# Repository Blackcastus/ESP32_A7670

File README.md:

# ph_portable_refrigerator_v2_hw

Designer: Mr.Duc_Hien

## Lưu ý thiết kế Hardware.
- Khóa cửa thường hở 12V (dài x rộng x cao tối thiểu 49mm x 30mm x 20mm). -> check notOK
- Vị trí cổng USB trên tủ thay bằng khay sim. -> check OK
- Thêm led status cho simcom và PGS.
- Sử dụng các loại header cắp khác nhau để không bị cắm nhầm.
- Kiếm lại lò xo cho button.
- Thiết kế lại bus cắm LCD.
- Chú ý căn chỉnh LCD cho khớp với vỏ tủ.
- Kiếm lại IC UART - I2C chp bộ BMS.
- Thêm RS485 viết bằng software uart.

## Hồ sơ đặc tả tủ lạnh di đông.

[Mô tả tủ lạnh di động](./Mota_TuLanhDiDong.pdf)

## Block diagram.

## Hardware MCU và Display

1. **Hardware board MCU.**

    **1.1. Thông số kỹ thuật board MCU:**

    * Nguồn input 12V được lấy từ bộ pin 12V hoặc qua adapter 12V.
    * MCU : ESP32-WROOM, debug qua USB.
    * Cảm biến: nhiệt độ PT100, cảm biến cửa.
    * Lấy vị trí GPS.
    * Kết nối module SIM 3G.
    * Đọc/lưu thời gian thực qua RTC.
    * Lưu dữ liệu vào thẻ nhớ.
    * Kết nối với màn hình LCD TFT 2Inch.
    * kết nối với bàn phím cảm ứng.
    * Có RS485 (sử dụng code software serial mới dùng được).
    * Điều khiển block lạnh.
    * Điều khiển khóa tủ.
    * Điều khiển đèn chiếu sáng trong tủ.
    * Điều khiểu chuông báo.
    * Đọc dữ liệu quản lý pin từ daly BMS.
    
    **1.2. Hình ảnh bộ quản lý pin BMS**

    **1.3. Hình ảnh board**

    Top layer

    Bottom layer

    Top 3D

    Bottom 3D

2. Hardware board display.

    **2.1. Thông số kỹ thuật board display**
    * Điện áp: 3V3.
    * Giao tiếp với LCD qua giao thức SPI.
    * Giao tiếp với bàn phím cảm ứng qua giao thức I2C.
    * Có chuông báo.

    **2.2. Hình ảnh board**

    Top layer

    Bottom layer

    Top 3D

    Bottom 3D

    Board sau khi hàn

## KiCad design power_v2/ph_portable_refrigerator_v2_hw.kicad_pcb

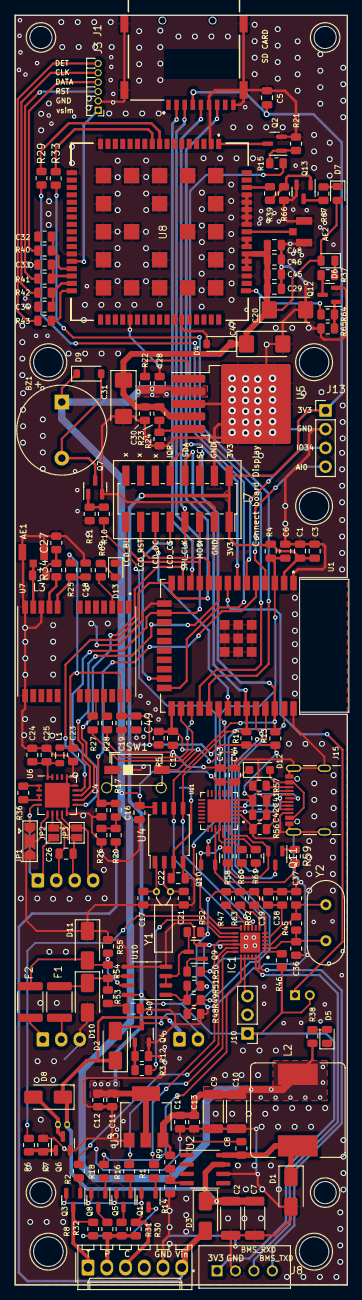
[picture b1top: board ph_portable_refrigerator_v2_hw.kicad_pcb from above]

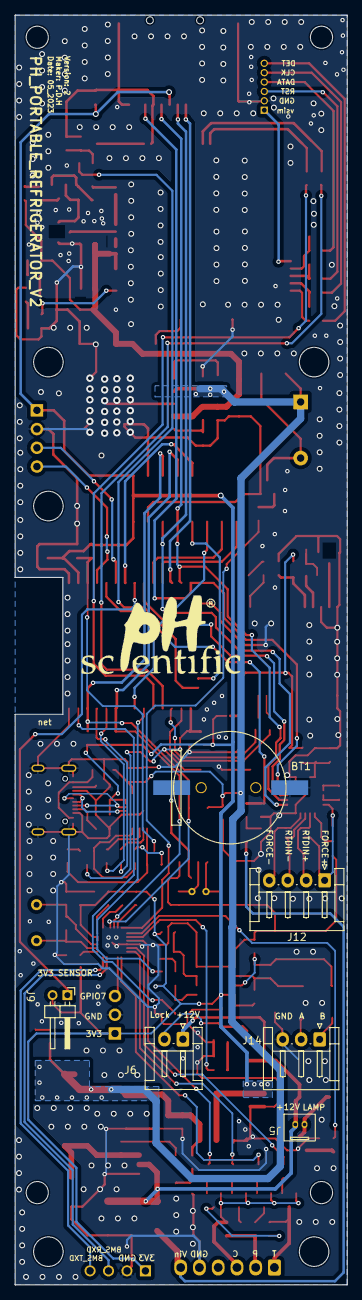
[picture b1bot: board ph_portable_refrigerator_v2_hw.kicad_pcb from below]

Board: 2 copper layers, 45.0 x 172.0 mm, 179 parts (6 on the bottom side), 131 nets.

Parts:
AE1: GPS; Antenna_RF
AE2: gsm; Antenna_RF
BT1: cr1220; BT_CR1220
BZ1: Buzzer-Device; Buzzer_12x9.5RM7.6
C1, C6, C15, C18, C22, C29, C41, C43: 10uF; C_0805_2012Metric
C2, C7, C9, C10: 10uF; R_2010_5025Metric
C3, C5, C16, C26, C40, C42, C44, C45, C49: 100nF; C_0805_2012Metric
C4, C12, C14, C25, C38: 100nF; R_0805_2012Metric
C8, C27: 10nF; R_0805_2012Metric
C11, C13, C28, C39: 10uF; R_0805_2012Metric
C17, C21: 7pF; R_0805_2012Metric
C19: 1uF; C_0805_2012Metric
C20, C31, C47: 100uF; CP_EIA-6032-15_Kemet-U
C23, C24, C30: 1uF; R_0805_2012Metric
C32, C33, C34: 22pF; R_0805_2012Metric
C36, C37: 18pF; R_0805_2012Metric
C46: 33pF; C_0805_2012Metric
C48: 10pF; C_0805_2012Metric
D1, D3: SS3x_SMA; D_SMA
D2: m7; D_SMA
D4: 5.1V; D_SOD-123
D5: RED; LED_0805_2012Metric
D6, D7, D13: blue; LED_0805_2012Metric
D8: M7; D_SMA
D9: 1N4148_T4; D_SOD-123
D10, D11: D_TVS; D_SMA
D12: 1N4007_T7; D_SOD-123F
F1, F2: Fuse; Fuse_SMD_1812
IC1: SC16IS750IBS,128; QFN50P400X400X100-25N
J1: microSD_Card
J3: Conn_01x06_Pin; PinHeader_1x06_P1.27mm_Horizontal
J5: lamp; Header_2P_1.25mm
J6: lock_latch; JST_EH_S2B-EH_1x02_P2.50mm_Horizontal
J7: Conn_02x08_Odd_Even; PinSocket_2x08_P2.00mm_Vertical_SMD
J8: Header_4P_2.54mm
J9: sensor; PinHeader_1x02_P2.00mm_Horizontal
J10: Extra; PinHeader_1x03_P2.54mm_Vertical
J11: refrigerator; Molex_KK-254_AE-6410-06A_1x06_P2.54mm_Vertical
J12: Conn_01x04; JST_EH_S4B-EH_1x04_P2.50mm_Horizontal
J13: Extra; PinHeader_1x04_P2.54mm_Vertical
J14: Conn_01x03_Pin; JST_EH_S3B-EH_1x03_P2.50mm_Horizontal
J15: USB_C_Receptacle_USB2.0; USB_C_Receptacle_GCT_USB4105-xx-A_16P_TopMnt_Horizontal
JP1: SolderJumper_3_Bridged12; SolderJumper-3_P2.0mm_Open_TrianglePad1.0x1.5mm
JP2, JP3: SolderJumper_2_Open; SolderJumper-2_P1.3mm_Open_Pad1.0x1.5mm
L1: L600R; L_0805_2012Metric
L2: 15uH; L_Bourns_SRR1260
L3: 22uH; R_0805_2012Metric
Q1, Q3, Q5, Q8, Q10, Q11: C1815; SOT-23
Q2, Q7, Q12, Q13: C1815_SOT23; SOT-23
Q4: AO3400A; SOT-23-3
Q6: AO3400A; SOT-23
Q9: 2SC1815-HF; SOT-23
R1, R2, R10, R15, R16, R17, R18, R26, R38, R45, R46, R47: 1k; R_0805_2012Metric
R3, R6: 100R; R_0805_2012Metric
R4: 10K; C_0805_2012Metric
R5, R7, R11, R12, R20, R21, R22, R58, R59: 10k; R_0805_2012Metric
R8: 680R; R_0805_2012Metric
R9: 10k1%; R_0805_2012Metric
R13, R19, R39, R49, R53, R55, R62, R63, R64: 4.7K; R_0805_2012Metric
R14: 4k7 1%; R_0805_2012Metric
R23: 240R/1%; R_0805_2012Metric
R24: 120R/1%; R_0805_2012Metric
R25: 10k; C_0805_2012Metric
R27: 22R; C_0805_2012Metric
R28, R29, R33, R40, R41, R42, R43: 22R; R_0805_2012Metric
R30: 47k; R_0805_2012Metric
R31: 4.7k; R_0805_2012Metric
R32: 810R; R_0805_2012Metric
R34: 10R; R_0805_2012Metric
R36: 400R; R_0805_2012Metric
R37, R67, R69: 1K; R_0805_2012Metric
R48, R51, R52: 10K; R_0805_2012Metric
R50: 2.2K; R_0805_2012Metric
R54: 120R; R_0805_2012Metric
R56, R57: 5.1K; R_0805_2012Metric
R60, R61: 470R; R_0805_2012Metric
R65, R66: 47K; R_0805_2012Metric
SW1: button_2pin; SW_DIP_SPSTx01_Slide_6.7x4.1mm_W6.73mm_P2.54mm_LowProfile_J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
U1: ESP32-WROOM; MODULE_ESP32-WROOM-32
U2: TPS5430DDAR; SOIC-8-1EP_3.9x4.9mm_P1.27mm_EP2.29x3mm_ThermalVias
U3: AMS1117-3.3; SOT-223-3_TabPin2
U4: DS1307Z+_SMD; SOIC-8W_5.3x5.3mm_P1.27mm
U5: MIC29302WU; TO-263-5_TabPin3
U6: MAX31865_TQFN; QFN-20-1EP_5x5mm_P0.65mm_EP3.35x3.35mm
U7: NEO-M8M; XCVR_NEO-M9N-00B
U8: SIM_COM_A7670; SimCom_A7670
U10: MAX485; SO-8_3.9x4.9mm_P1.27mm
U11: CP2102-GM; CP2102
Y1: 32.768; Crystal_DS26_D2.0mm_L6.0mm_Horizontal
Y2: 14.7456 MHz; Crystal_HC49-4H_Vertical

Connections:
+3V3: C1.1, C3.1, C5.1, C11.1, C12.1, C19.1, C23.1, C38.2, C39.2, C40.2, C41.1, C42.1, C49.1, IC1.4 (VDD), IC1.5 (I2C/SPI), J1.P4 (VDD), J7.1, J7.2, J8.1, J9.2, J10.1, J13.1, L1.1, R4.2, R5.1, R13.1, R19.1, R25.1, R46.2, R47.1, R51.1, R52.1, R53.1, R62.2, R63.2, U1.2 (3V3), U3.2 (VO), U7.23 (VCC), U10.8 (VCC), U11.6 (VDD), U11.7 (REGIN)
+3V8: C20.1, C29.1, C30.1, C31.1, C45.1, C46.1, C47.1, C48.1, D4.1 (K), D6.1 (A), D7.1 (A), R23.1, U5.4 (VOUT), U8.55 (VBAT_1), U8.56 (VBAT_2), U8.57 (VBAT_3)
+5V: BZ1.1 (-), C9.1, C10.1, C13.1, C14.1, C16.1, C28.1, C43.1, C44.1, D9.1 (K), D12.1 (K), L2.2, R9.1, R22.1, R38.2, U3.3 (VI), U4.8 (VCC), U5.2 (VIN), U11.8 (VBUS)
+12V: C2.1, C7.1, D2.1 (K), D3.1 (K), D8.1 (K), J5.1, J6.1, U2.7 (VIN)
+BATT: BT1.1, C22.1, U4.3 (VBAT)
/AI01: C4.1, R17.1, U1.5 (SENSOR_VN)
/ESP_RX: R61.1, U1.34 (RXD0)
/ESP_TX: R60.1, U1.35 (TXD0)
/GPS/Timepluse: R69.1, U7.3 (TIMEPULSE)
/GPS/gps_ant: AE1.1 (A), L3.2, U7.11 (RF_IN)
/GPS/vRF: R34.1, U7.9 (VCC_RF)
/GPS_RXD: R28.1, U1.27 (IO16)
/GPS_TXD: R27.1, U1.26 (IO4)
/GSM Block/NetLight: R64.1, U8.52 (NETLIGHT)
/GSM Block/Status: R39.1, U8.66 (STATUS)
/GSM Block/VSIM: J3.1, U8.30 (SIM_VDD)
/GSM Block/pwrkey: Q2.3 (C), U8.1 (PWRKEY)
/GSM Block/sim_clk: C33.1, R41.1, U8.32 (SIM_CLK)
/GSM Block/sim_clk#: J3.3, R41.2
/GSM Block/sim_data: C32.1, R40.1, U8.31 (SIM_DATA)
/GSM Block/sim_data#: J3.4, R40.2
/GSM Block/sim_det: R43.1, U8.34 (SIM_DET)
/GSM Block/sim_det#: J3.6, R43.2
/GSM Block/sim_rst: C34.1, R42.1, U8.33 (SIM_RST)
/GSM Block/sim_rst#: J3.5, R42.2
/GSM_PWR_KEY: R15.1, U1.24 (IO2)
/GSM_RXD: R33.1, U1.29 (IO5)
/GSM_TXD: R29.1, U1.28 (IO17)
/I2C Expand Block/BMS_RXD: IC1.23 (TX), J8.3
/I2C Expand Block/BMS_TXD: IC1.24 (RX), J8.4
/I2C Expand Block/Buzzer: IC1.12 (GPIO0), R10.1
/I2C Expand Block/C: J11.3, Q1.2 (E), Q3.2 (E), Q5.2 (E), Q8.2 (E), R30.1
/I2C Expand Block/Lamp: IC1.13 (GPIO1), R6.1
/I2C Expand Block/Lock: IC1.14 (GPIO2), R3.1
/I2C Expand Block/P: J11.2, R30.2, R31.2, R32.2
/I2C Expand Block/P1: IC1.15 (GPIO3), R1.1
/I2C Expand Block/P2: IC1.17 (GPIO4/~DSR), R2.1
/I2C Expand Block/P3: IC1.18 (GPIO5/~DTR), R16.1
/I2C Expand Block/P4: IC1.19 (GPIO6/~CD), R18.1
/I2C Expand Block/T: J11.1, Q3.3 (C), R8.2
/I2C Expand Block/Vin: D3.2 (A), J11.6, R20.2
/I2C Expand Block/a0/cs: IC1.6 (A0/CS), R62.1
/I2C Expand Block/a1/si: IC1.7 (A1/SI), R63.1
/I2C Expand Block/gpio7/ri: IC1.20 (GPIO7/RI), J10.3
/I2C_SCL: IC1.9 (SCL), J7.6, R13.2, U1.36 (IO22), U4.6 (SCL)
/I2C_SDA: IC1.10 (SDA/VSS), J7.8, R19.2, U1.33 (IO21), U4.5 (SDA)
/LCD_BL: J7.15, U1.11 (IO26)
/LCD_CS: J7.9, U1.23 (IO15)
/LCD_DC: J7.11, U1.31 (IO19)
/LCD_RST: J7.13, U1.10 (IO25)
/MCU Block/AI00: J13.4, U1.4 (SENSOR_VP)
/MCU Block/CP_DTR: Q11.2 (E), R58.2, U11.28 (~DTR)
/MCU Block/CP_RST: Q10.2 (E), R59.2, U11.24 (~RST)
/MCU Block/CP_RXD: R60.2, U11.25 (RXD)
/MCU Block/CP_TXD: R61.2, U11.26 (TXD)
/MCU Block/IO34: J13.3, U1.6 (IO34)
/MCU Block/USB_D+: J15.A6 (D+), J15.B6 (D+), U11.4 (D+)
/MCU Block/USB_D-: J15.A7 (D-), J15.B7 (D-), U11.5 (D–)
/SENSOR_DOOR: J9.1, U1.8 (IO32)
/SOFTWARE_RXD: R48.2, R49.1, U1.37 (IO23)
/SOFTWARE_TXD: R50.1, U1.30 (IO18)
/SPI_CLK: J1.P5 (CLK), J7.7, U1.13 (IO14), U6.12 (SCLK)
/SPI_MAX_CS: U1.9 (IO33), U6.13 (~CS)
/SPI_MISO: J1.P7 (DAT0), U1.14 (IO12), U6.14 (SDO)
/SPI_MOSI: J1.P3 (CMD), J7.5, U1.16 (IO13), U6.11 (SDI)
/SPI_SD_CS: J1.P2 (CD/DAT3), U1.12 (IO27)
/TS_IQR: J7.10, U1.7 (IO35)
/Uart to RS485/A: F1.2, J14.2
/Uart to RS485/B: F2.2, J14.1
ESP_EN: C6.1, Q10.3 (C), R4.1, U1.3 (EN)
ESP_IO0: C15.1, Q11.3 (C), R5.2, SW1.2, U1.25 (IO0)
GND: AE1.2 (Shield), AE1.3 (Shield), AE2.2 (Shield), AE2.3 (Shield), BT1.2, C1.2, C2.2, C3.2, C4.2, C5.2, C6.2, C7.2, C9.2, C10.2, C11.2, C12.2, C13.2, C14.2, C15.2, C16.2, C17.1, C18.2, C19.2, C20.2, C21.1, C22.2, C23.2, C24.2, C25.2, C27.2, C28.2, C29.2, C30.2, C31.2, C32.2, C33.2, C34.2, C36.1, C37.1, C38.1, C39.1, C40.1, C41.2, C42.2, C43.2, C44.2, C45.2, C46.2, C47.2, C48.2, C49.2, D1.2 (A), D4.2 (A), D5.2 (K), D10.2 (A2), D11.1 (A1), D13.2 (K), IC1.16 (VSS), IC1.25 (GND), J1.P6 (VSS), J1.P9 (CD), J1.SH1 (SHIELD), J1.SH2 (SHIELD), J1.SH3 (SHIELD), J1.SH4 (SHIELD), J3.2, J7.3, J7.4, J8.2, J10.2, J11.5, J13.2, J14.3, J15.A1 (GND), J15.A8 (SBU1), J15.A12 (GND), J15.B1 (GND), J15.B8 (SBU2), J15.B12 (GND), J15.S1 (SHIELD), JP1.3 (B), Q2.2 (E), Q4.2 (S), Q6.2 (S), Q7.2 (E), Q9.2 (E), Q12.2 (E), Q13.2 (E), R7.1, R11.1, R12.1, R14.2, R21.2, R24.2, R26.1, R48.1, R55.2, R56.1, R57.1, R65.1, R66.1, SW1.1, U1.1 (GND), U1.15 (GND), U1.38 (GND), U1.39_1, U1.39_2, U1.39_3, U1.39_4, U1.39_5, U1.39_6, U1.39_7, U1.39_8, U1.39_9, U2.6 (GND), U3.1 (GND), U4.4 (GND), U5.3 (GND), U6.10 (GND2), U6.15 (DGND), U6.16 (GND1), U6.21 (PAD), U7.10 (GND), U7.12 (GND), U7.13 (GND), U7.24 (GND), U8.2 (GND_1), U8.17 (GND_2), U8.18 (GND_3), U8.29 (GND_4), U8.39 (GND_5), U8.45 (GND_6), U8.46 (GND_7), U8.54 (GND_8), U8.58 (GND_9), U8.59 (GND_10), U8.61 (GND_11), U8.62 (GND_12), U8.63 (GND_13), U8.64 (GND_14), U8.65 (GND_15), U8.69 (GND_16), U8.70 (GND_17), U8.71 (GND_18), U8.72 (GND_19), U8.73 (GND_20), U8.74 (GND_21), U8.75 (GND_22), U8.76 (GND_23), U8.77 (GND_24), U8.78 (GND_25), U8.79 (GND_26), U8.80 (GND_27), U8.81 (GND_28), U8.82 (GND_29), U8.83 (GND_30), U8.84 (GND_31), U8.85 (GND_32), U8.86 (GND_33), U8.87 (GND_34), U8.88 (GND_35), U10.4 (DI), U10.5 (GND), U11.3 (GND), U11.29 (GND)
unnamed: AE2.1 (A), U8.60 (RF_ANT)
unnamed: BZ1.2 (+), D9.2 (A), Q7.3 (C)
unnamed: C27.1, L3.1, R34.2
unnamed: C8.2, D1.1 (K), L2.1, U2.8 (PH)
unnamed: D2.2 (A), J6.2, Q4.3 (D)
unnamed: D5.1 (A), R38.1
unnamed: D6.2 (K), R37.2
unnamed: D7.2 (K), R67.2
unnamed: D8.2 (A), J5.2, Q6.3 (D)
unnamed: D10.1 (A1), F1.1, R53.2, R54.1, U10.6 (A)
unnamed: D11.2 (A2), F2.1, R54.2, R55.1, U10.7 (B)
unnamed: D12.2 (A), J15.A4 (VBUS), J15.A9 (VBUS), J15.B4 (VBUS), J15.B9 (VBUS)
unnamed: D13.1 (A), R69.2
unnamed: C36.2, IC1.2 (XTAL1), R45.2, Y2.2
unnamed: C37.2, IC1.3 (XTAL2), R45.1, Y2.1
unnamed: IC1.11 (~IRQ), R47.2
unnamed: IC1.1 (~RESET), R46.1
unnamed: J12.1, JP1.1 (A), JP2.2 (B), U6.5 (FORCE+)
unnamed: C26.1, J12.2, JP2.1 (A), U6.7 (RTDIN+)
unnamed: C26.2, J12.3, JP3.2 (B), U6.8 (RTDIN-)
unnamed: J12.4, JP3.1 (A), U6.9 (FORCE-)
unnamed: J15.A5 (CC1), R56.2
unnamed: J15.B5 (CC2), R57.2
unnamed: JP1.2 (C), U6.6 (FORCE2)
unnamed: Q1.1 (B), R1.2
unnamed: Q1.3 (C), R8.1
unnamed: Q2.1 (B), R15.2, R21.1
unnamed: Q3.1 (B), R2.2
unnamed: Q4.1 (G), R3.2, R12.2
unnamed: Q5.1 (B), R16.2
unnamed: Q5.3 (C), R31.1
unnamed: Q6.1 (G), R6.2, R7.2
unnamed: Q7.1 (B), R10.2, R11.2
unnamed: Q8.1 (B), R18.2
unnamed: Q8.3 (C), R32.1
unnamed: Q9.1 (B), R50.2
unnamed: Q9.3 (C), R52.2, U10.2 (~RE), U10.3 (DE)
unnamed: Q10.1 (B), R58.1
unnamed: Q11.1 (B), R59.1
unnamed: Q12.1 (B), R64.2, R65.2
unnamed: Q12.3 (C), R37.1
unnamed: Q13.1 (B), R39.2, R66.2
unnamed: Q13.3 (C), R67.1
unnamed: R17.2, R20.1, R26.2
unnamed: C8.1, U2.1 (BOOT)
unnamed: R9.2, R14.1, U2.4 (VSENSE)
unnamed: C17.2, U4.1 (X1), Y1.1
unnamed: C21.2, U4.2 (X2), Y1.2
unnamed: R23.2, R24.1, U5.5 (ADJ)
unnamed: R22.2, U5.1 (EN)
unnamed: R36.1, U6.1 (BIAS), U6.2 (REFIN+)
unnamed: C24.1, C25.1, L1.2, U6.19 (DVDD), U6.20 (VDD)
unnamed: R36.2, U6.3 (REFIN-), U6.4 (ISENSOR)
unnamed: R28.2, U7.21 (RXD/SPI_MOSI)
unnamed: R27.2, U7.20 (TXD/SPI_MISO)
unnamed: C18.1, R25.2, U7.8 (~RESET)
unnamed: R33.2, U8.10 (RXD)
unnamed: R29.2, U8.9 (TXD)
unnamed: R49.2, R51.2, U10.1 (RO)

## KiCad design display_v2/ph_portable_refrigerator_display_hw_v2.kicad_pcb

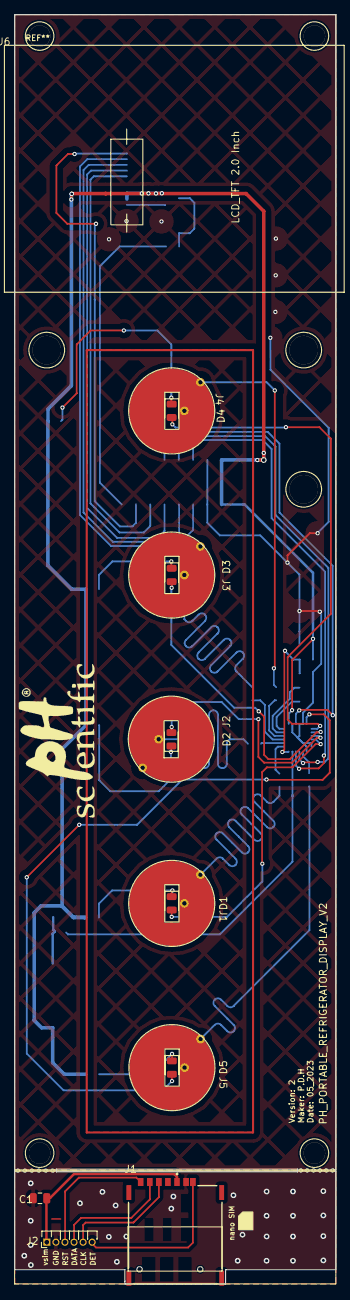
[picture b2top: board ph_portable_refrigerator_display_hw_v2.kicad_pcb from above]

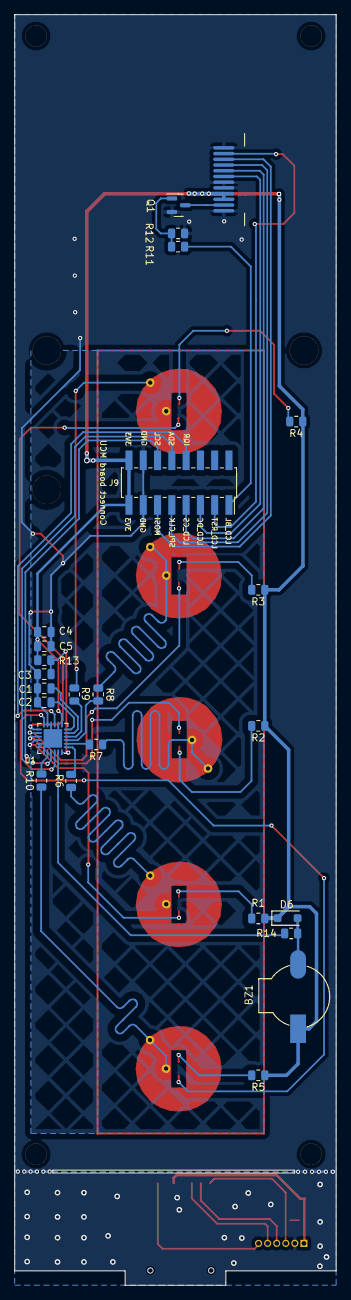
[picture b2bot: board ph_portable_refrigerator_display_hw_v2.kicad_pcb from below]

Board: 2 copper layers, 45.0 x 177.8 mm, 38 parts (24 on the bottom side), 38 nets.

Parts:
BZ1: Buzzer-Device; Buzzer_SMD_9633
C1, C2, C3, C4: 100nF; C_0805_2012Metric
C1#2: 2.2nF; C_0805_2012Metric
C5: 10uF; C_0805_2012Metric
D1, D2, D3, D4, D5: LED0805; LED_0805_2012Metric
D6: 1N4007_T7; D_SOD-123F
J1: SIM7100-6-1-15-00-A_REVC; microSIM_Card
J1#2, J2#2, J3, J4, J5: Conn_01x01; Button_Touch_Circle
J2: Conn_01x06_Pin; PinHeader_1x06_P1.27mm_Horizontal
J6: LCD12PIN; LCD_TFT_34.6x47.6mm_2INCH
J9: Conn_02x08_Odd_Even; PinSocket_2x08_P2.00mm_Vertical_SMD
Q1: C1815_SOT23; SOT-23
R1, R2, R3, R4, R5, R14: 1k; R_0805_2012Metric
R6, R7, R8, R9, R10: 560R; R_0805_2012Metric
R11: 100R; R_0805_2012Metric
R12, R13: 10k; R_0805_2012Metric
U1: CY8CMBR3116; QFN-24-1EP_4x4mm_P0.5mm_EP2.6x2.6mm

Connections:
+3V3: BZ1.1 (-), C4.1, C5.1, D6.1 (K), J6.3 (LEDA), J6.4 (VDD), J9.15, J9.16, R1.1, R2.1, R3.1, R4.1, R5.1, R13.1, U1.7 (VDD)
/i2c_scl: J9.12, U1.22 (SCL)
/i2c_sda: J9.10, U1.21 (SDA)
/lcd_bl: J9.1, R11.1
/lcd_clk: J6.9 (SCL), J9.9
/lcd_cs: J6.8 (CS), J9.7
/lcd_dc: J6.7 (D/C), J9.5
/lcd_mosi: J6.10 (SDA), J9.11
/lcd_rst: J6.11 (RST), J9.3
/ts1: J1#2.1, R6.1
/ts2: J2#2.1, R7.1
/ts3: J3.1, R8.1
/ts4: J4.1, R9.1
/ts5: J5.1, R10.1
/ts_irq: J9.8, U1.9 (CS15)
GND: C1.2, C1#2.2, C2.2, C3.2, C4.2, C5.2, J1.C5 (GND), J2.2, J6.1 (GND), J6.5 (GND), J6.6 (GND), J6.12 (GND), J9.13, J9.14, Q1.2 (E), R12.2, U1.8 (VSS), U1.10 (CS14), U1.11 (CS13), U1.17 (CS7), U1.18 (CS6), U1.19 (CS5), U1.25 (EP)
unnamed: BZ1.2 (+), D6.2 (A), R14.2
unnamed: D1.1 (A), R1.2
unnamed: D1.2 (K), U1.16 (CS8)
unnamed: D2.1 (A), R2.2
unnamed: D2.2 (K), U1.15 (CS9)
unnamed: D3.1 (A), R3.2
unnamed: D3.2 (K), U1.14 (CS10)
unnamed: D4.1 (A), R4.2
unnamed: D4.2 (K), U1.13 (CS11)
unnamed: D5.1 (A), R5.2
unnamed: D5.2 (K), U1.12 (CS12)
unnamed: J6.2 (LEDK), Q1.3 (C)
unnamed: Q1.1 (B), R11.2, R12.1
unnamed: C1#2.1, U1.5 (CMOD)
unnamed: R6.2, U1.1 (CS0)
unnamed: R7.2, U1.2 (CS1)
unnamed: R8.2, U1.3 (CS2)
unnamed: R9.2, U1.4 (CS3)
unnamed: R10.2, U1.20 (CS4)
unnamed: C2.1, U1.6 (VCC)
unnamed: R14.1, U1.23 (~HI)
unnamed: C3.1, R13.2, U1.24 (~XRES)

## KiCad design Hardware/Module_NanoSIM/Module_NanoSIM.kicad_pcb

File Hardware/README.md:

Designer: Mr.Duc_Hien

## Lưu ý thiết kế Hardware.
- Khóa cửa thường hở 12V (dài x rộng x cao tối thiểu 49mm x 30mm x 20mm). -> check notOK
- Vị trí cổng USB trên tủ thay bằng khay sim. -> check OK
- Thêm led status cho simcom và PGS.
- Sử dụng các loại header cắp khác nhau để không bị cắm nhầm.
- Kiếm lại lò xo cho button.
- Thiết kế lại bus cắm LCD.
- Chú ý căn chỉnh LCD cho khớp với vỏ tủ.
- Kiếm lại IC UART - I2C chp bộ BMS.
- Thêm RS485 viết bằng software uart.

## Block diagram.

## Hardware MCU và Display

1. **Hardware board MCU.**

    **1.1. Thông số kỹ thuật board MCU:**

    * Nguồn input 12V được lấy từ bộ pin 12V hoặc qua adapter 12V.
    * MCU : ESP32-WROOM, debug qua USB.
    * Cảm biến: nhiệt độ PT100, cảm biến cửa.
    * Lấy vị trí GPS.
    * Kết nối module SIM 3G.
    * Đọc/lưu thời gian thực qua RTC.
    * Lưu dữ liệu vào thẻ nhớ.
    * Kết nối với màn hình LCD TFT 2Inch.
    * kết nối với bàn phím cảm ứng.
    * Có RS485 (sử dụng code software serial mới dùng được).
    * Điều khiển block lạnh.
    * Điều khiển khóa tủ.
    * Điều khiển đèn chiếu sáng trong tủ.
    * Điều khiểu chuông báo.
    * Đọc dữ liệu quản lý pin từ daly BMS.
    
    **1.2. Hình ảnh bộ quản lý pin BMS**

    **1.3. Hình ảnh board**

    Top layer

    Bottom layer

    Top 3D

    Bottom 3D

2. Hardware board display.

    **2.1. Thông số kỹ thuật board display**
    * Điện áp: 3V3.
    * Giao tiếp với LCD qua giao thức SPI.
    * Giao tiếp với bàn phím cảm ứng qua giao thức I2C.
    * Có chuông báo.

    **2.2. Hình ảnh board**

    Top layer

    Bottom layer

    Top 3D

    Bottom 3D

    Board sau khi hàn

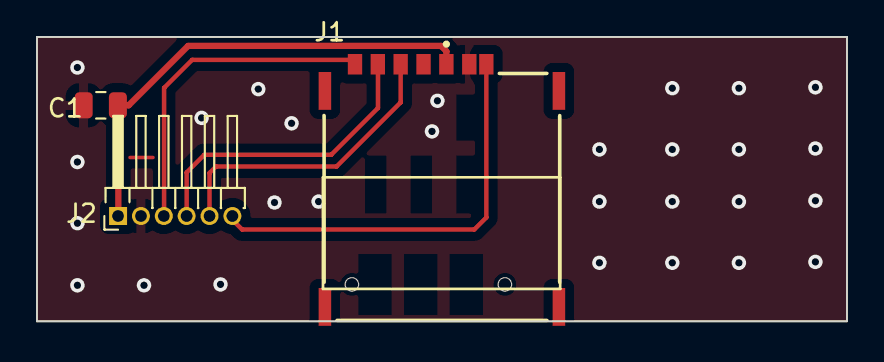
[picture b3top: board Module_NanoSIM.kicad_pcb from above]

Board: 2 copper layers, 45.0 x 15.8 mm, 3 parts (0 on the bottom side), 6 nets.

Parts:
C1: 100nF; C_0805_2012Metric
J1: SIM7100-6-1-15-00-A_REVC; microSIM_Card
J2: Conn_01x06_Pin; PinHeader_1x06_P1.27mm_Horizontal

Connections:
/VSIM: C1.1, J1.C1 (VCC), J2.1
/sim_clk#: J1.C3 (CLK), J2.3
/sim_data#: J1.C7 (I/O), J2.4
/sim_det#: J1.CD, J2.6
/sim_rst#: J1.C2 (RST), J2.5
GND: C1.2, J1.C5 (GND), J2.2

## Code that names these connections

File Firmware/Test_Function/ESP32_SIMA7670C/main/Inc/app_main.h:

#ifndef _APP_MAIN_H_
#define _APP_MAIN_H_

/* library system */

#include <stdio.h>
#include <stdint.h>
#include <string.h>

/* config module sim GSM */
#define GSM_PWR_KEY (GPIO_NUM_2)
#define GSM_TXD (GPIO_NUM_5)
#define GSM_RXD (GPIO_NUM_17)
#define GSM_UART_PORT (UART_NUM1)
#define GSM_BAUD_RATE (115200)

/* void function task */
void GSM_Init();
void GSM_Write_CMD(const char *logName, const char *data);
void GSM_Read_Data(const char *logName);

#endif

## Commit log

2023-05-18 layout PCB MCU, layout PCB display, edit nanosim
2023-05-18 modify README.md: add block diagram
2023-05-19 Add Ho so dac ta tu lanh di dong
2023-05-22 Oder PCB, Viet tai lieu mo ta hardware
2023-06-08 Han Board MCU va board Display
2023-06-09 Modify tx/rx UART0, LED GPS, pin rst/clk sim card
2023-06-09 create folder Hardware
2023-06-10 Test function esp32-s7670c
